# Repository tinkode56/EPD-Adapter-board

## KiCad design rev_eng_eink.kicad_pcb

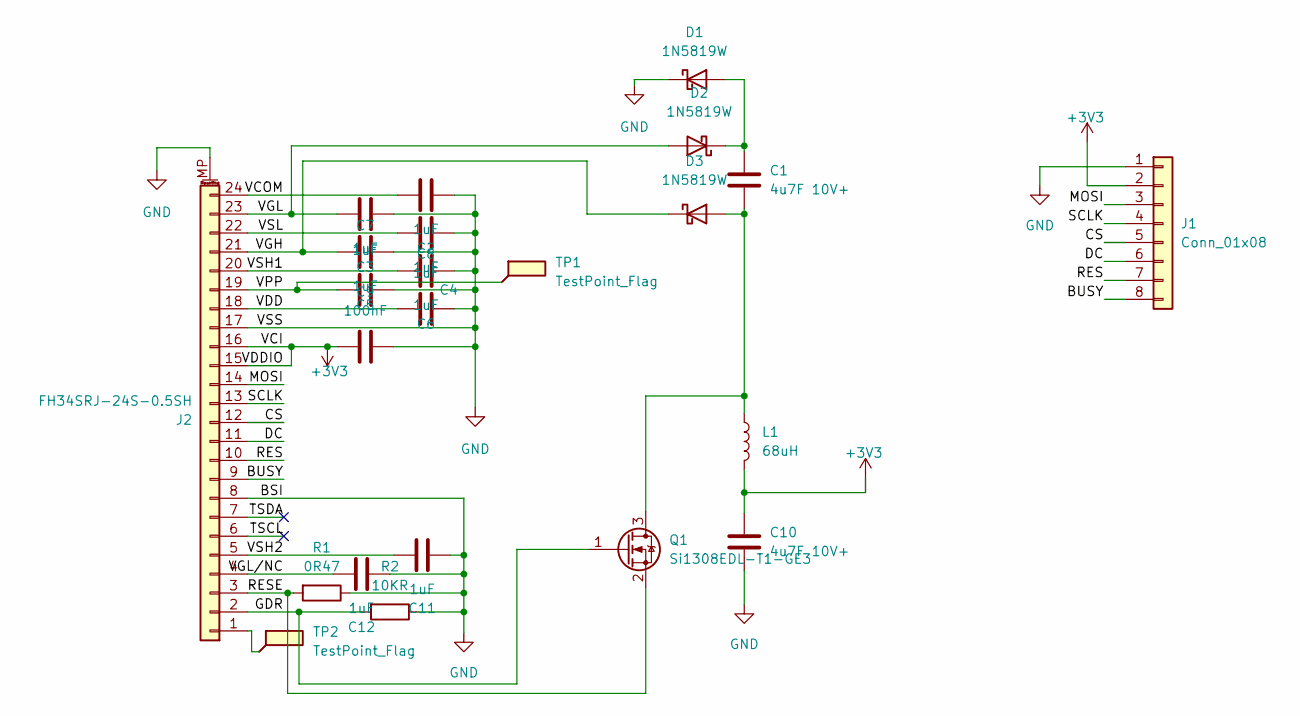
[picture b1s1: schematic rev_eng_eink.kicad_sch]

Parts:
C1, C10: 4u7F 10V+; C_0603_1608Metric_Pad1.08x0.95mm_HandSolder; Manufacturer part CL10A475KO8NNNC
C2, C3, C4, C5, C6, C7, C8, C11, C12: 1uF; C_0603_1608Metric_Pad1.08x0.95mm_HandSolder; Manufacturer part CL10A105KO8NNNC
C9: 100nF; C_0603_1608Metric_Pad1.08x0.95mm_HandSolder; Manufacturer part TCC0603X7R104K500CT
D1, D2, D3: 1N5819W; D_SOD-123; Manufacturer part 1N5819W
J1: Conn_01x08; Harwin_M20-89008xx_1x08_P2.54mm_Horizontal
J2: FH34SRJ-24S-0.5SH; Hirose_FH12-24S-0.5SH_1x24-1MP_P0.50mm_Horizontal; Manufacturer part FH34SRJ-24S-0.5SH
L1: 68uH; L_0805_2012Metric_Pad1.15x1.40mm_HandSolder; Manufacturer part MLF2012C380KT000
Q1: Si1308EDL-T1-GE3; SOT-323_SC-70_Handsoldering; Manufacturer part Si1308EDL-T1-GE3
R1: 0R47; R_0603_1608Metric_Pad0.98x0.95mm_HandSolder; Manufacturer part 0603WAJ047KT5E
R2: 10KR; R_0603_1608Metric_Pad0.98x0.95mm_HandSolder; Manufacturer part RS-03K103JT
TP1, TP2: TestPoint_Flag; TestPoint_Pad_1.0x1.0mm

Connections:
+3V3: C9.2, C10.2, J1.2, J2.15, J2.16, L1.2
/BUSY: J1.8, J2.9
/CS: J1.5, J2.12
/DC: J1.6, J2.11
/GDR: J2.2, Q1.1 (G), R2.2
/MOSI: J1.3, J2.14
/RES: J1.7, J2.10
/RESE: J2.3, Q1.2 (S), R1.2
/SCLK: J1.4, J2.13
/TSCL: J2.6
/TSDA: J2.7
/VCOM: C2.2, J2.24
/VDD: C8.2, J2.18
/VGH: C5.2, D3.1 (K), J2.21
/VGL: C3.2, D2.2 (A), J2.23
/VGL/NC: C12.2, J2.4
/VPP: C7.1, J2.19, TP1.1
/VSH1: C6.2, J2.20
/VSH2: C11.2, J2.5
/VSL: C4.2, J2.22
GND: C2.1, C3.1, C4.1, C5.1, C6.1, C7.2, C8.1, C9.1, C10.1, C11.1, C12.1, D1.1 (K), J1.1, J2.8, J2.17, J2.MP (MountPin), R1.1, R2.1
unnamed: C1.1, D3.2 (A), L1.1, Q1.3 (D)
unnamed: C1.2, D1.2 (A), D2.1 (K)
unnamed: J2.1, TP2.1

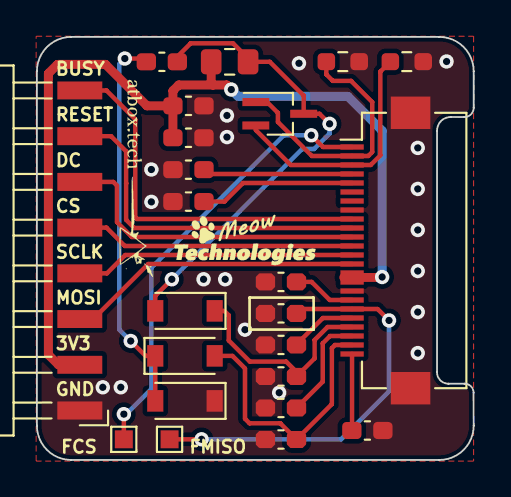
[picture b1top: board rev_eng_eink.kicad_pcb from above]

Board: 2 copper layers, 24.3 x 23.5 mm, 24 parts (1 on the bottom side), 22 nets.

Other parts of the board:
kibuzzard-62D83402: G***; kibuzzard-62D83402
